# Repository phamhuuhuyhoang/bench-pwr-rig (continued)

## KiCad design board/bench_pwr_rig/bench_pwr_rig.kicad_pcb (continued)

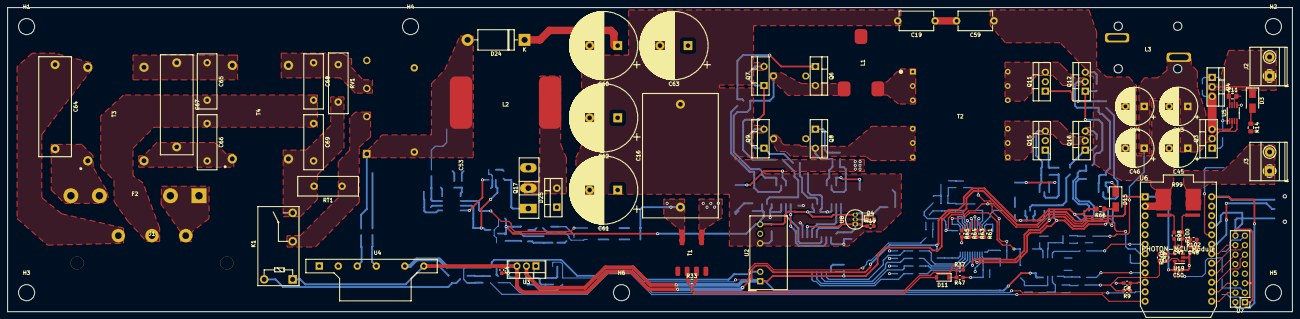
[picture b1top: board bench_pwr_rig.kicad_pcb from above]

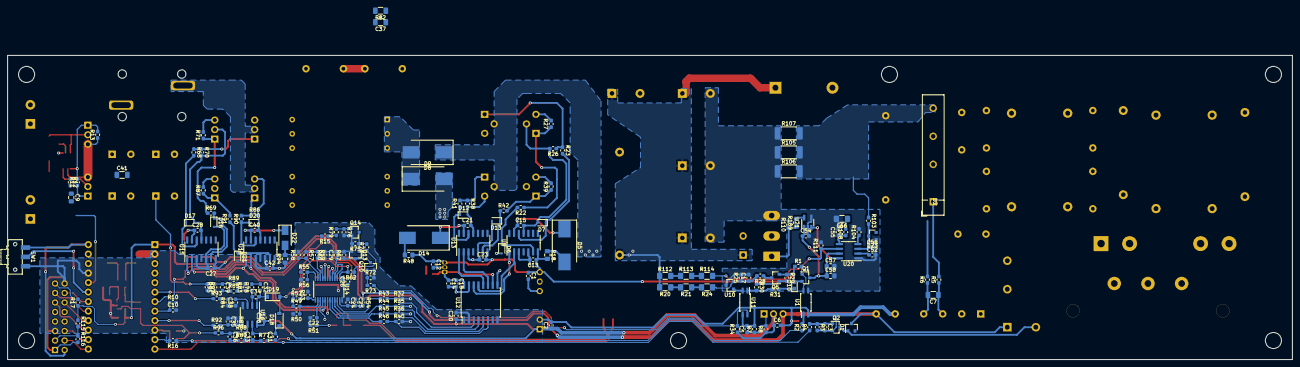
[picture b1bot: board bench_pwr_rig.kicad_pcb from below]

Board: 2 copper layers, 343.4 x 81.3 mm, 268 parts (182 on the bottom side), 160 nets.

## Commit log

2020-10-17 added kicad project
    initial creation of kicad project
    added schematic
    added board file
2020-10-18 Use photon
    Updated schematic to use particle photon device for 3.3V interface to existing NHD-0208AZ-RN-YBW-3V in stock
2020-10-23 Updated powertrain schematic
    Changed powertrain to PSFB
    Updated schematic
    Added new symbols
2020-10-23 Delete buck_boost.sch
    Delete unused schematic
2020-10-28 Schematic Update
    Updated schematic
    Added Input Filter and PFC sections
    Added capacitor, resistor, and protection parts library
    Started a jupyter notebook for PFC section
2020-11-07 schematic and layout updates
    Finalized schematic for rev 0.1. Anticipate additional component values update through analysis. Moving to layout
2020-11-18 Updated layout
    Added output screw terminal
    Added mounting screws M4
    Changed primary ground to secondary ground plane coupling capacitor to radial disc type with safety rating X1, Y1
    Continued layout
